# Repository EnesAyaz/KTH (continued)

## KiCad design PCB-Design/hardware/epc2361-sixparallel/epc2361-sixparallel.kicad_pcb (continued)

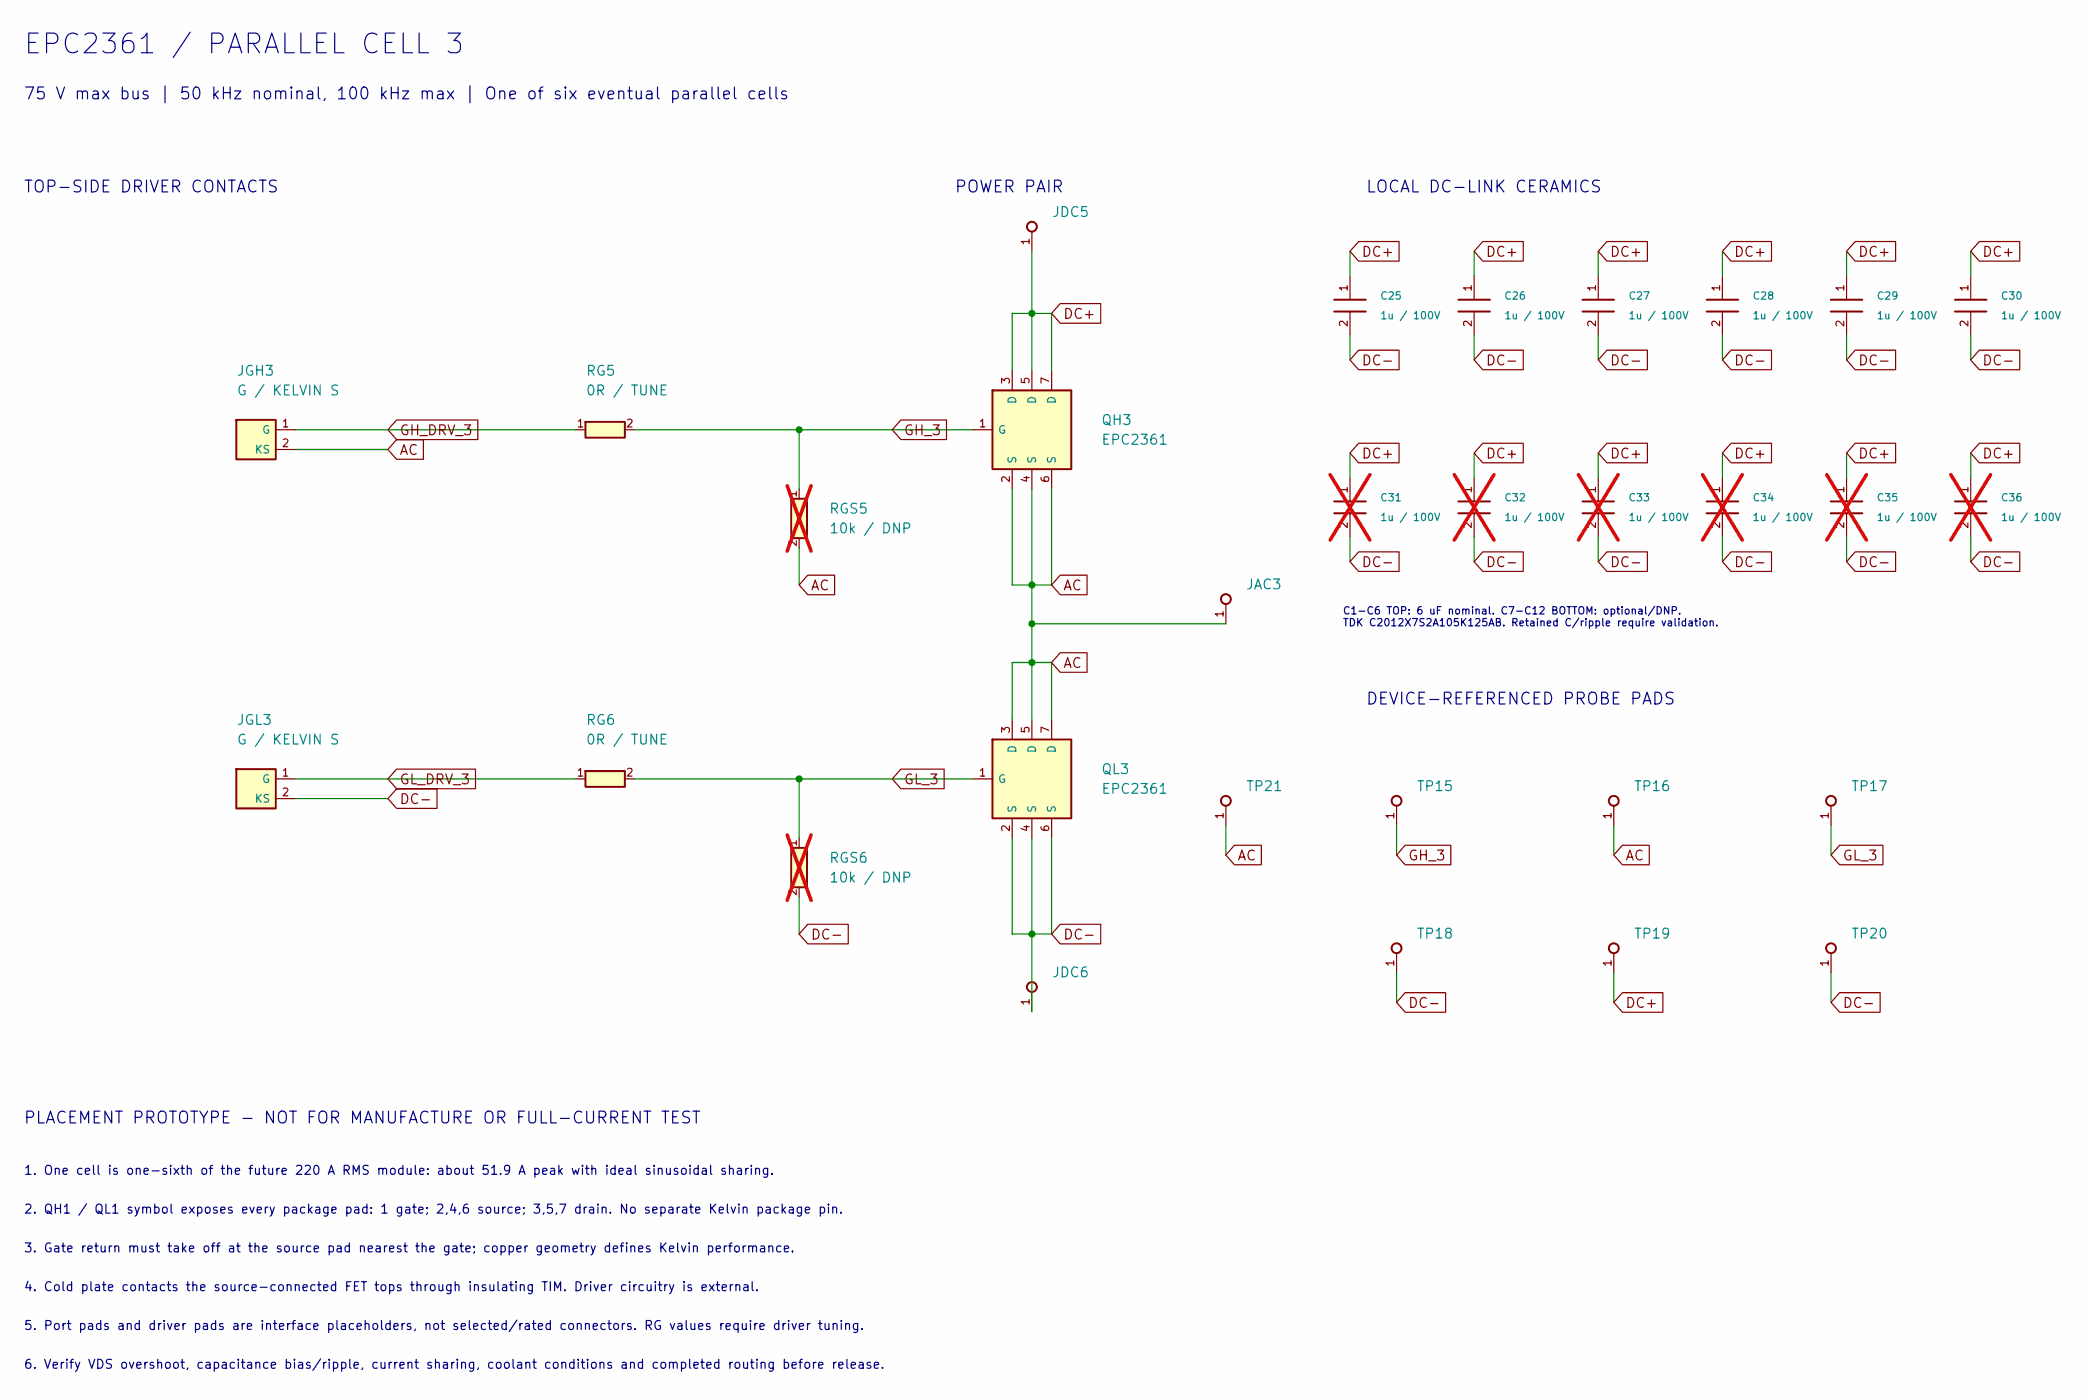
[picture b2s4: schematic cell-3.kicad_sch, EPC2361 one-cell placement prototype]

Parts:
C25, C26, C27, C28, C29, C30: 1u / 100V; C_0805_2012Metric
C31, C32, C33, C34, C35, C36: 1u / 100V; C_0805_2012Metric; not fitted
JAC3: AC PORT PAD; Power_Port_Pad
JDC5: DC+ PORT PAD; Power_Port_Pad
JDC6: DC- PORT PAD; Power_Port_Pad
JGH3: G / KELVIN S; Gate_Source_Pads
JGL3: G / KELVIN S; Gate_Source_Pads
QH3: EPC2361
QL3: EPC2361
RG5, RG6: 0R / TUNE; R_0402_1005Metric
RGS5, RGS6: 10k / DNP; R_0402_1005Metric; not fitted
TP15: GH; Probe_Pad
TP16, TP21: AC; Probe_Pad
TP17: GL; Probe_Pad
TP18, TP20: DC-; Probe_Pad
TP19: DC+; Probe_Pad

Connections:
AC: JAC3.1, JGH3.2 (KS), QH3.2 (S), QH3.4 (S), QH3.6 (S), QL3.3 (D), QL3.5 (D), QL3.7 (D), RGS5.2, TP16.1, TP21.1; also elsewhere on the board
DC+: C25.1, C26.1, C27.1, C28.1, C29.1, C30.1, C31.1, C32.1, C33.1, C34.1, C35.1, C36.1, JDC5.1, QH3.3 (D), QH3.5 (D), QH3.7 (D), TP19.1; also elsewhere on the board
DC-: C25.2, C26.2, C27.2, C28.2, C29.2, C30.2, C31.2, C32.2, C33.2, C34.2, C35.2, C36.2, JDC6.1, JGL3.2 (KS), QL3.2 (S), QL3.4 (S), QL3.6 (S), RGS6.2, TP18.1, TP20.1; also elsewhere on the board
GH_3: QH3.1 (G), RG5.2, RGS5.1, TP15.1
GH_DRV_3: JGH3.1 (G), RG5.1
GL_3: QL3.1 (G), RG6.2, RGS6.1, TP17.1
GL_DRV_3: JGL3.1 (G), RG6.1

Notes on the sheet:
EPC2361 / PARALLEL CELL 3
75 V max bus | 50 kHz nominal, 100 kHz max | One of six eventual parallel cells
TOP-SIDE DRIVER CONTACTS
POWER PAIR
LOCAL DC-LINK CERAMICS
C1-C6 TOP: 6 uF nominal. C7-C12 BOTTOM: optional/DNP. TDK C2012X7S2A105K125AB. Retained C/ripple require validation.
DEVICE-REFERENCED PROBE PADS
PLACEMENT PROTOTYPE - NOT FOR MANUFACTURE OR FULL-CURRENT TEST
1. One cell is one-sixth of the future 220 A RMS module: about 51.9 A peak with ideal sinusoidal sharing.
2. QH1 / QL1 symbol exposes every package pad: 1 gate; 2,4,6 source; 3,5,7 drain. No separate Kelvin package pin.
3. Gate return must take off at the source pad nearest the gate; copper geometry defines Kelvin performance.
4. Cold plate contacts the source-connected FET tops through insulating TIM. Driver circuitry is external.
5. Port pads and driver pads are interface placeholders, not selected/rated connectors. RG values require driver tuning.
6. Verify VDS overshoot, capacitance bias/ripple, current sharing, coolant conditions and completed routing before release.

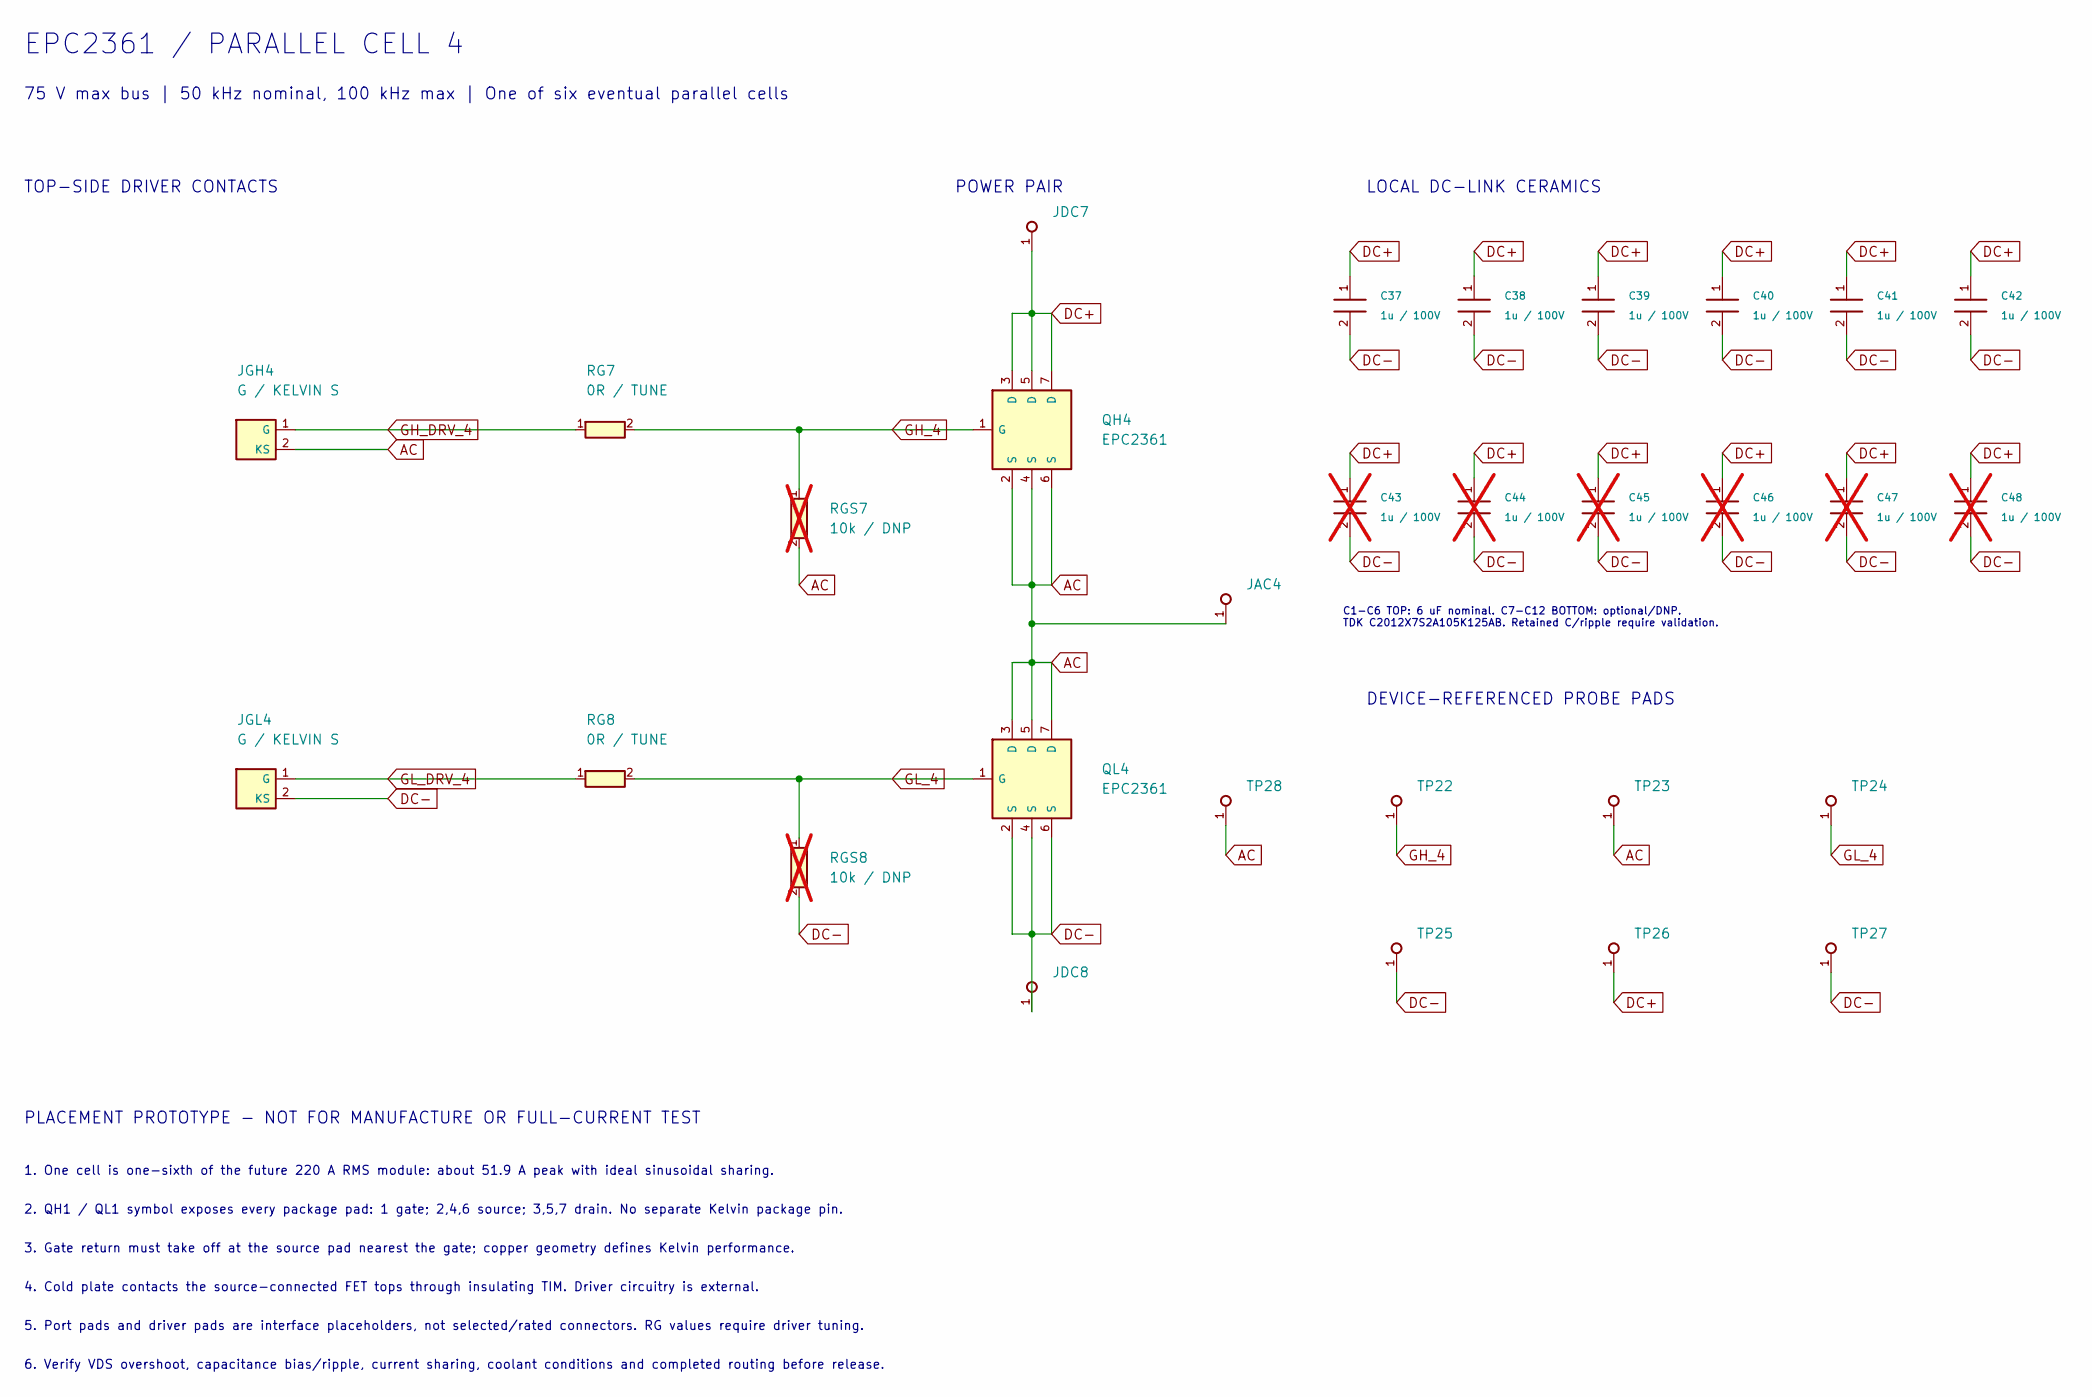
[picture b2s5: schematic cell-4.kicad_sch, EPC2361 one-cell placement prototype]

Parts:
C37, C38, C39, C40, C41, C42: 1u / 100V; C_0805_2012Metric
C43, C44, C45, C46, C47, C48: 1u / 100V; C_0805_2012Metric; not fitted
JAC4: AC PORT PAD; Power_Port_Pad
JDC7: DC+ PORT PAD; Power_Port_Pad
JDC8: DC- PORT PAD; Power_Port_Pad
JGH4: G / KELVIN S; Gate_Source_Pads
JGL4: G / KELVIN S; Gate_Source_Pads
QH4: EPC2361
QL4: EPC2361
RG7, RG8: 0R / TUNE; R_0402_1005Metric
RGS7, RGS8: 10k / DNP; R_0402_1005Metric; not fitted
TP22: GH; Probe_Pad
TP23, TP28: AC; Probe_Pad
TP24: GL; Probe_Pad
TP25, TP27: DC-; Probe_Pad
TP26: DC+; Probe_Pad

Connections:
AC: JAC4.1, JGH4.2 (KS), QH4.2 (S), QH4.4 (S), QH4.6 (S), QL4.3 (D), QL4.5 (D), QL4.7 (D), RGS7.2, TP23.1, TP28.1; also elsewhere on the board
DC+: C37.1, C38.1, C39.1, C40.1, C41.1, C42.1, C43.1, C44.1, C45.1, C46.1, C47.1, C48.1, JDC7.1, QH4.3 (D), QH4.5 (D), QH4.7 (D), TP26.1; also elsewhere on the board
DC-: C37.2, C38.2, C39.2, C40.2, C41.2, C42.2, C43.2, C44.2, C45.2, C46.2, C47.2, C48.2, JDC8.1, JGL4.2 (KS), QL4.2 (S), QL4.4 (S), QL4.6 (S), RGS8.2, TP25.1, TP27.1; also elsewhere on the board
GH_4: QH4.1 (G), RG7.2, RGS7.1, TP22.1
GH_DRV_4: JGH4.1 (G), RG7.1
GL_4: QL4.1 (G), RG8.2, RGS8.1, TP24.1
GL_DRV_4: JGL4.1 (G), RG8.1

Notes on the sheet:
EPC2361 / PARALLEL CELL 4
75 V max bus | 50 kHz nominal, 100 kHz max | One of six eventual parallel cells
TOP-SIDE DRIVER CONTACTS
POWER PAIR
LOCAL DC-LINK CERAMICS
C1-C6 TOP: 6 uF nominal. C7-C12 BOTTOM: optional/DNP. TDK C2012X7S2A105K125AB. Retained C/ripple require validation.
DEVICE-REFERENCED PROBE PADS
PLACEMENT PROTOTYPE - NOT FOR MANUFACTURE OR FULL-CURRENT TEST
1. One cell is one-sixth of the future 220 A RMS module: about 51.9 A peak with ideal sinusoidal sharing.
2. QH1 / QL1 symbol exposes every package pad: 1 gate; 2,4,6 source; 3,5,7 drain. No separate Kelvin package pin.
3. Gate return must take off at the source pad nearest the gate; copper geometry defines Kelvin performance.
4. Cold plate contacts the source-connected FET tops through insulating TIM. Driver circuitry is external.
5. Port pads and driver pads are interface placeholders, not selected/rated connectors. RG values require driver tuning.
6. Verify VDS overshoot, capacitance bias/ripple, current sharing, coolant conditions and completed routing before release.

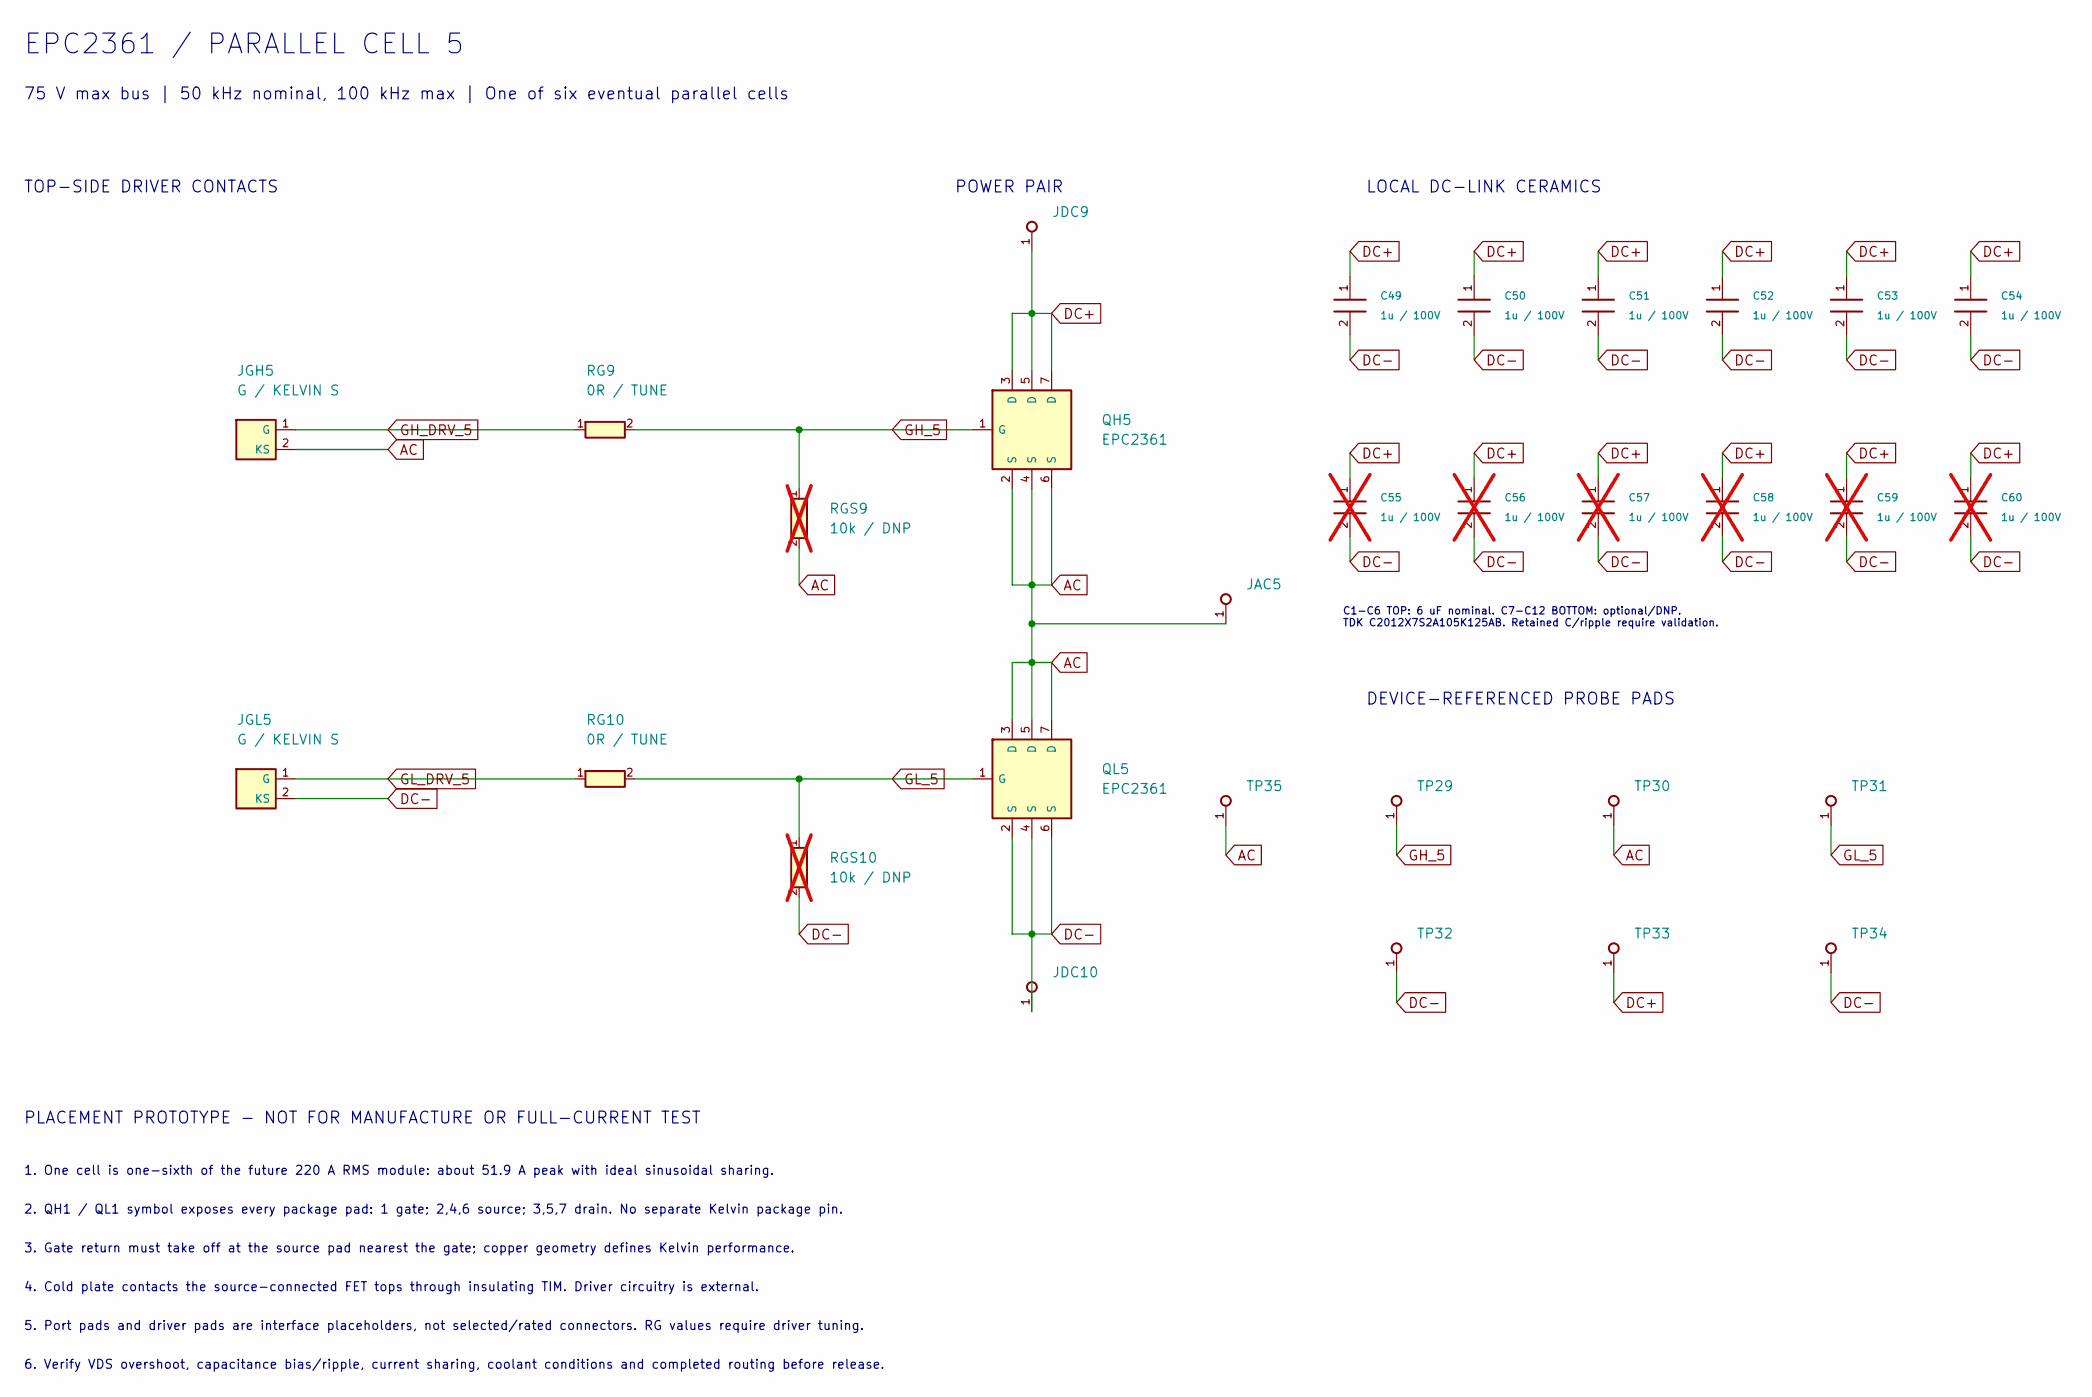
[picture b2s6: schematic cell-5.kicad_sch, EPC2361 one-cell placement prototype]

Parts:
C49, C50, C51, C52, C53, C54: 1u / 100V; C_0805_2012Metric
C55, C56, C57, C58, C59, C60: 1u / 100V; C_0805_2012Metric; not fitted
JAC5: AC PORT PAD; Power_Port_Pad
JDC9: DC+ PORT PAD; Power_Port_Pad
JDC10: DC- PORT PAD; Power_Port_Pad
JGH5: G / KELVIN S; Gate_Source_Pads
JGL5: G / KELVIN S; Gate_Source_Pads
QH5: EPC2361
QL5: EPC2361
RG9, RG10: 0R / TUNE; R_0402_1005Metric
RGS9, RGS10: 10k / DNP; R_0402_1005Metric; not fitted
TP29: GH; Probe_Pad
TP30, TP35: AC; Probe_Pad
TP31: GL; Probe_Pad
TP32, TP34: DC-; Probe_Pad
TP33: DC+; Probe_Pad

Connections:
AC: JAC5.1, JGH5.2 (KS), QH5.2 (S), QH5.4 (S), QH5.6 (S), QL5.3 (D), QL5.5 (D), QL5.7 (D), RGS9.2, TP30.1, TP35.1; also elsewhere on the board
DC+: C49.1, C50.1, C51.1, C52.1, C53.1, C54.1, C55.1, C56.1, C57.1, C58.1, C59.1, C60.1, JDC9.1, QH5.3 (D), QH5.5 (D), QH5.7 (D), TP33.1; also elsewhere on the board
DC-: C49.2, C50.2, C51.2, C52.2, C53.2, C54.2, C55.2, C56.2, C57.2, C58.2, C59.2, C60.2, JDC10.1, JGL5.2 (KS), QL5.2 (S), QL5.4 (S), QL5.6 (S), RGS10.2, TP32.1, TP34.1; also elsewhere on the board
GH_5: QH5.1 (G), RG9.2, RGS9.1, TP29.1
GH_DRV_5: JGH5.1 (G), RG9.1
GL_5: QL5.1 (G), RG10.2, RGS10.1, TP31.1
GL_DRV_5: JGL5.1 (G), RG10.1

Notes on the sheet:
EPC2361 / PARALLEL CELL 5
75 V max bus | 50 kHz nominal, 100 kHz max | One of six eventual parallel cells
TOP-SIDE DRIVER CONTACTS
POWER PAIR
LOCAL DC-LINK CERAMICS
C1-C6 TOP: 6 uF nominal. C7-C12 BOTTOM: optional/DNP. TDK C2012X7S2A105K125AB. Retained C/ripple require validation.
DEVICE-REFERENCED PROBE PADS
PLACEMENT PROTOTYPE - NOT FOR MANUFACTURE OR FULL-CURRENT TEST
1. One cell is one-sixth of the future 220 A RMS module: about 51.9 A peak with ideal sinusoidal sharing.
2. QH1 / QL1 symbol exposes every package pad: 1 gate; 2,4,6 source; 3,5,7 drain. No separate Kelvin package pin.
3. Gate return must take off at the source pad nearest the gate; copper geometry defines Kelvin performance.
4. Cold plate contacts the source-connected FET tops through insulating TIM. Driver circuitry is external.
5. Port pads and driver pads are interface placeholders, not selected/rated connectors. RG values require driver tuning.
6. Verify VDS overshoot, capacitance bias/ripple, current sharing, coolant conditions and completed routing before release.

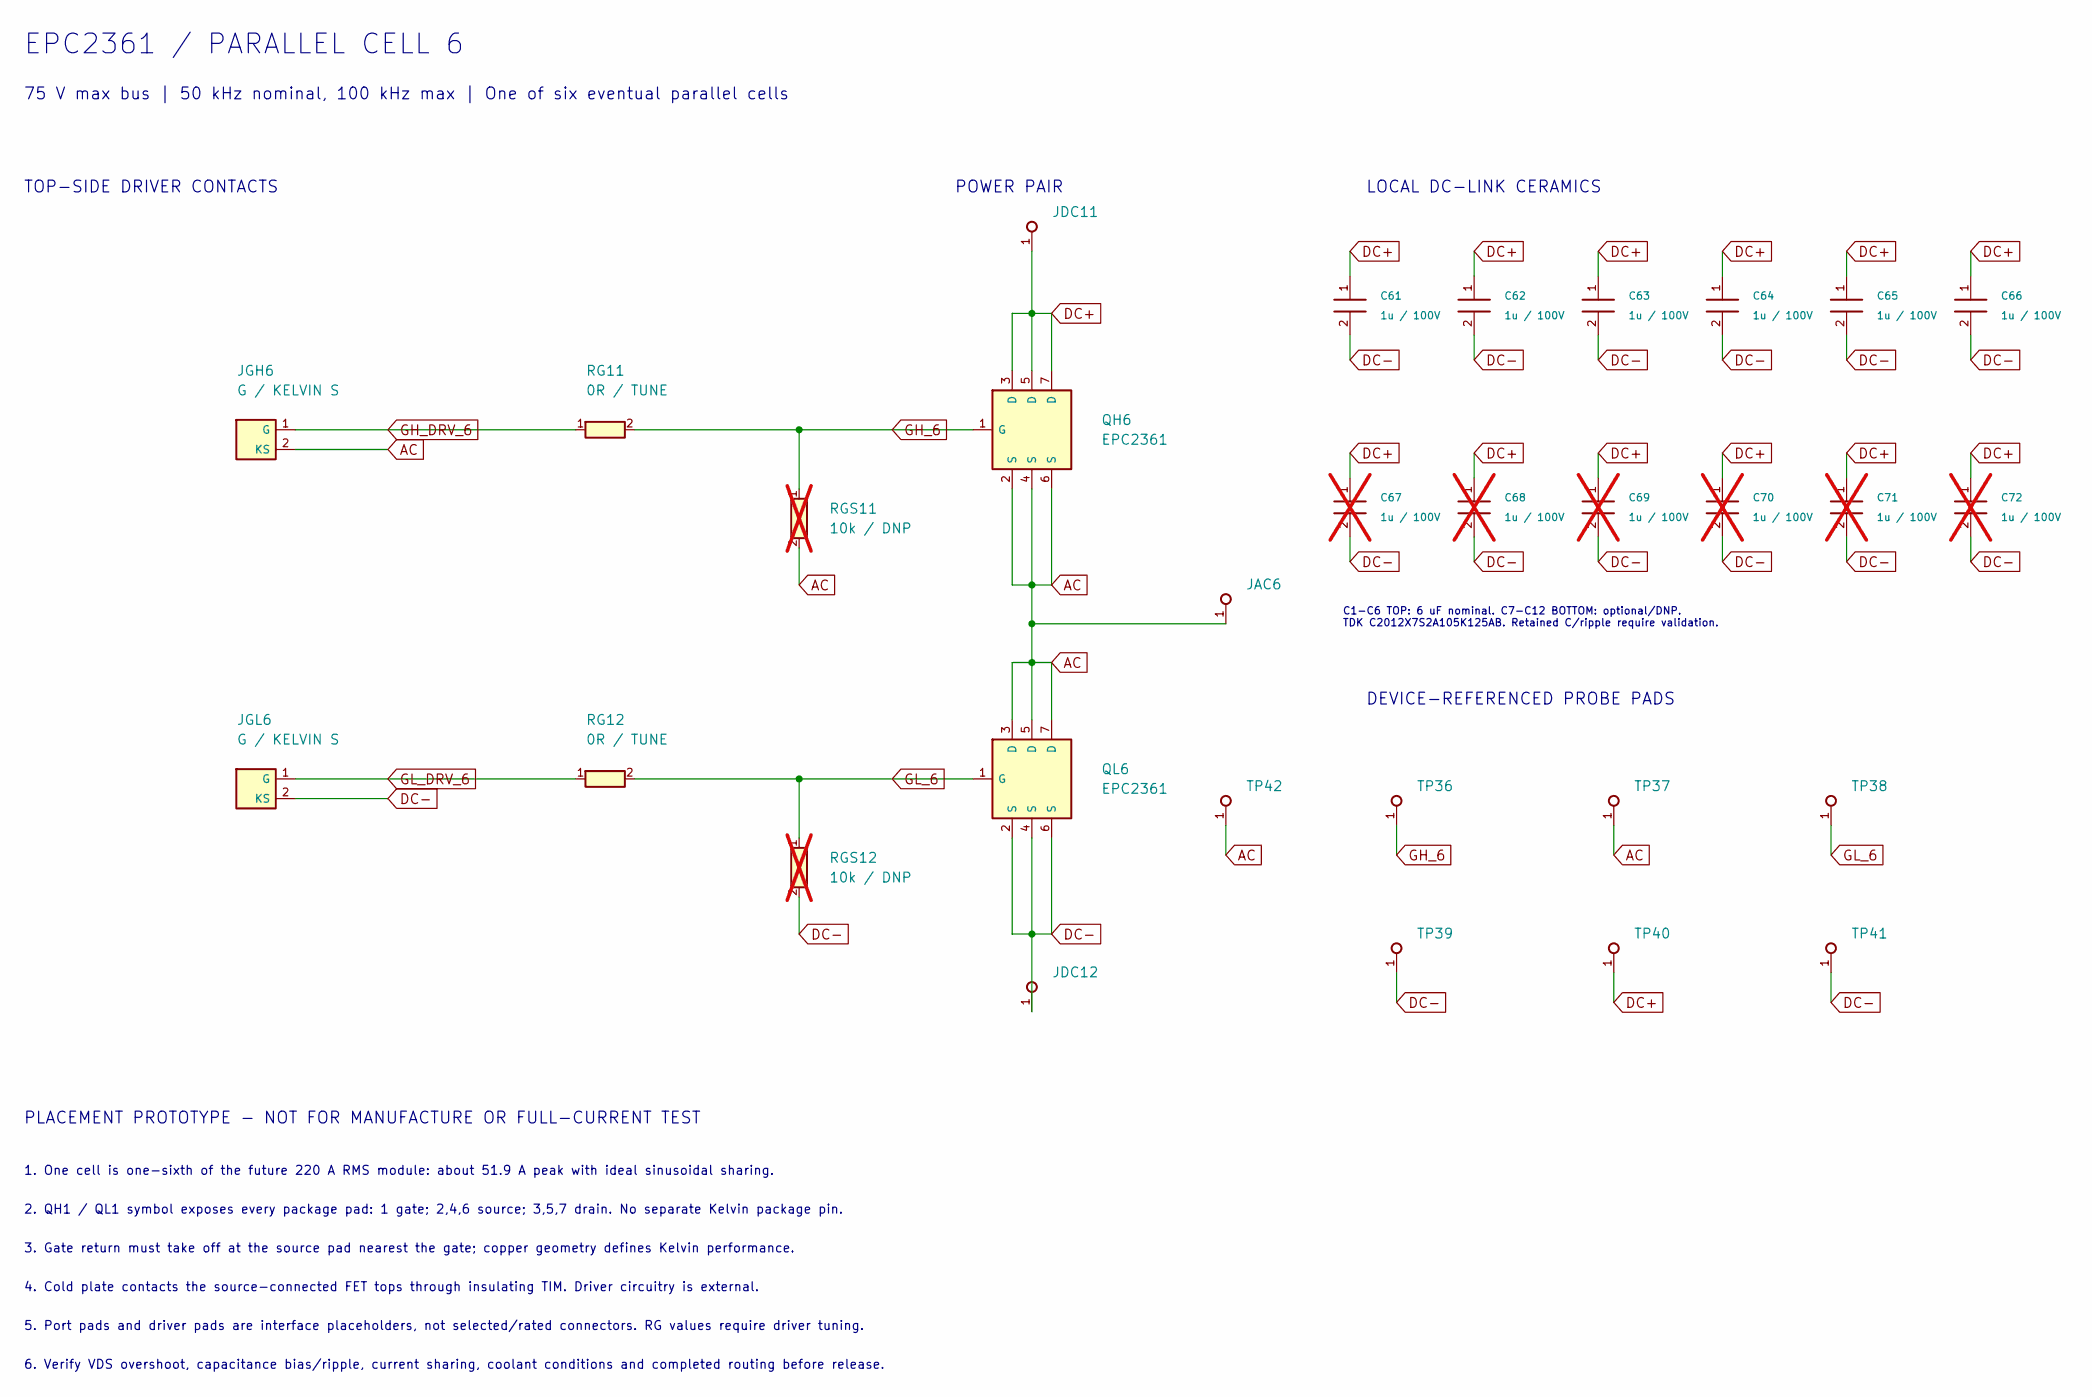
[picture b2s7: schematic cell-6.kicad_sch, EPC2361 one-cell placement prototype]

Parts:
C61, C62, C63, C64, C65, C66: 1u / 100V; C_0805_2012Metric
C67, C68, C69, C70, C71, C72: 1u / 100V; C_0805_2012Metric; not fitted
JAC6: AC PORT PAD; Power_Port_Pad
JDC11: DC+ PORT PAD; Power_Port_Pad
JDC12: DC- PORT PAD; Power_Port_Pad
JGH6: G / KELVIN S; Gate_Source_Pads
JGL6: G / KELVIN S; Gate_Source_Pads
QH6: EPC2361
QL6: EPC2361
RG11, RG12: 0R / TUNE; R_0402_1005Metric
RGS11, RGS12: 10k / DNP; R_0402_1005Metric; not fitted
TP36: GH; Probe_Pad
TP37, TP42: AC; Probe_Pad
TP38: GL; Probe_Pad
TP39, TP41: DC-; Probe_Pad
TP40: DC+; Probe_Pad

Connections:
AC: JAC6.1, JGH6.2 (KS), QH6.2 (S), QH6.4 (S), QH6.6 (S), QL6.3 (D), QL6.5 (D), QL6.7 (D), RGS11.2, TP37.1, TP42.1; also elsewhere on the board
DC+: C61.1, C62.1, C63.1, C64.1, C65.1, C66.1, C67.1, C68.1, C69.1, C70.1, C71.1, C72.1, JDC11.1, QH6.3 (D), QH6.5 (D), QH6.7 (D), TP40.1; also elsewhere on the board
DC-: C61.2, C62.2, C63.2, C64.2, C65.2, C66.2, C67.2, C68.2, C69.2, C70.2, C71.2, C72.2, JDC12.1, JGL6.2 (KS), QL6.2 (S), QL6.4 (S), QL6.6 (S), RGS12.2, TP39.1, TP41.1; also elsewhere on the board
GH_6: QH6.1 (G), RG11.2, RGS11.1, TP36.1
GH_DRV_6: JGH6.1 (G), RG11.1
GL_6: QL6.1 (G), RG12.2, RGS12.1, TP38.1
GL_DRV_6: JGL6.1 (G), RG12.1

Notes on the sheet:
EPC2361 / PARALLEL CELL 6
75 V max bus | 50 kHz nominal, 100 kHz max | One of six eventual parallel cells
TOP-SIDE DRIVER CONTACTS
POWER PAIR
LOCAL DC-LINK CERAMICS
C1-C6 TOP: 6 uF nominal. C7-C12 BOTTOM: optional/DNP. TDK C2012X7S2A105K125AB. Retained C/ripple require validation.
DEVICE-REFERENCED PROBE PADS
PLACEMENT PROTOTYPE - NOT FOR MANUFACTURE OR FULL-CURRENT TEST
1. One cell is one-sixth of the future 220 A RMS module: about 51.9 A peak with ideal sinusoidal sharing.
2. QH1 / QL1 symbol exposes every package pad: 1 gate; 2,4,6 source; 3,5,7 drain. No separate Kelvin package pin.
3. Gate return must take off at the source pad nearest the gate; copper geometry defines Kelvin performance.
4. Cold plate contacts the source-connected FET tops through insulating TIM. Driver circuitry is external.
5. Port pads and driver pads are interface placeholders, not selected/rated connectors. RG values require driver tuning.
6. Verify VDS overshoot, capacitance bias/ripple, current sharing, coolant conditions and completed routing before release.

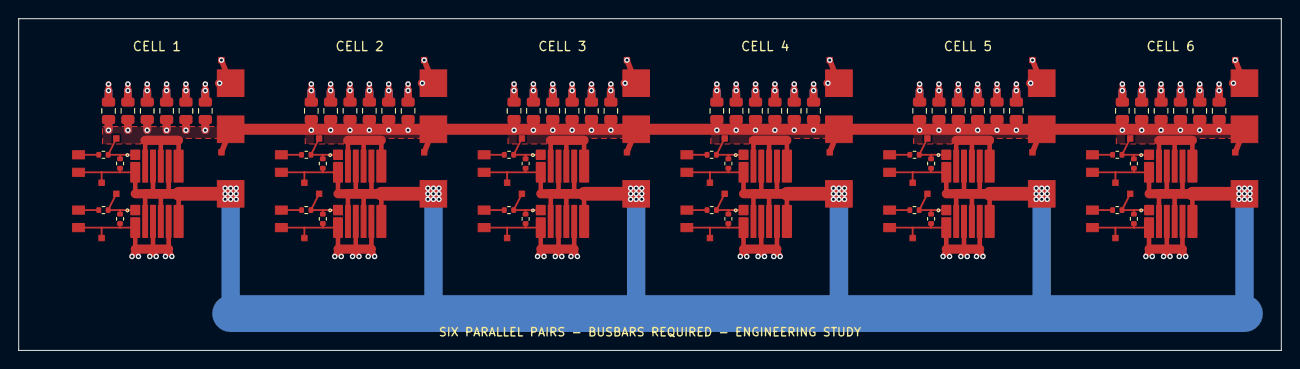
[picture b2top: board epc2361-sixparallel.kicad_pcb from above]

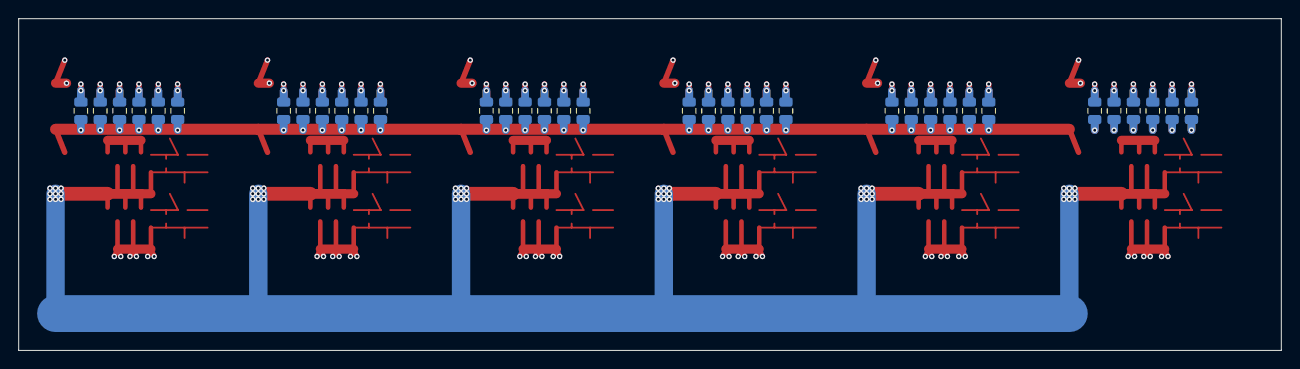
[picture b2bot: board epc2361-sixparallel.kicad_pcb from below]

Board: 4 copper layers, 137.0 x 36.0 mm, 180 parts (36 on the bottom side), 27 nets.

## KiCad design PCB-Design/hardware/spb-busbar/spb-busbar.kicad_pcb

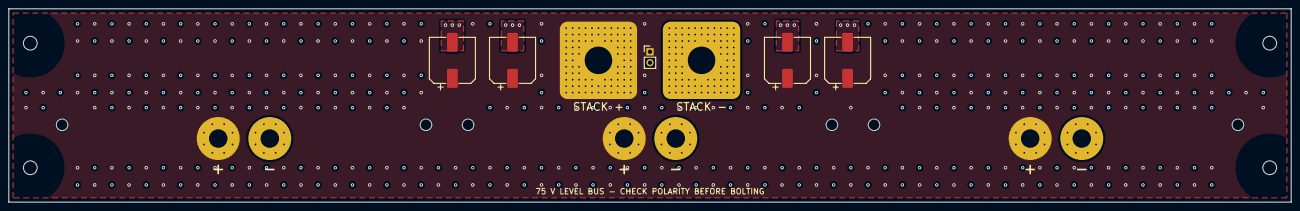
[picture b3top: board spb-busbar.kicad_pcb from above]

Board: 4 copper layers, 298.5 x 45.0 mm, 23 parts (0 on the bottom side), 2 nets, no tracks yet.

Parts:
C1, C2, C3, C4: DNP: 100 V hybrid polymer ~20-30 mOhm ESR (dampin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; CP_Elec_10x10.5
H1, H2, H3, H4, H5, H6: nylon M2.5 standoff 6.5 mm (leg H3/H4); MountingHole_2.7mm_M2.5
H7, H8, H9, H10: M3 insulating standoff to frame (8 mm Cu keep-out); MountingHole_3.2mm_M3
J1: LEG1 DC+; BUS_M4_REDCUBE
J2: LEG1 DC-; BUS_M4_REDCUBE
J3: LEG2 DC+; BUS_M4_REDCUBE
J4: LEG2 DC-; BUS_M4_REDCUBE
J5: LEG3 DC+; BUS_M4_REDCUBE
J6: LEG3 DC-; BUS_M4_REDCUBE
J7: STACK DC+ (to level above: its DC-); BUS_LUG_M6
J8: STACK DC- (to level below: its DC+); BUS_LUG_M6
J9: LEVEL V: 1 DC+, 2 DC- (HV referenced); PinHeader_1x02_P2.54mm_Vertical

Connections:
DCN: C1.2, C2.2, C3.2, C4.2, J2.1, J4.1, J6.1, J8.1, J9.2
DCP: C1.1, C2.1, C3.1, C4.1, J1.1, J3.1, J5.1, J7.1, J9.1

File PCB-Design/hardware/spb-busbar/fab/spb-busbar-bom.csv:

"# 4 layers, 1.6 mm FR4, 2 oz on all layers (JLC3313 stack-up), ENIG, bolt pads without mask"
Qty,References,Value,Footprint,Manufacturer part / note,Fit
1,J9,"LEVEL V: 1 DC+, 2 DC- (HV referenced)",PinHeader_1x02_P2.54mm_Vertical,2.54 mm header 1x2,fit
4,C1 C2 C3 C4,"DNP: 100 V hybrid polymer ~20-30 mOhm ESR (damping, fit if ringing)",CP_Elec_10x10.5,"select: 100 V hybrid polymer, 10 x 10.5 mm SMD",DNP

Mechanical (not placed by the assembler)
6,J1-J6,M4 x 8 screw + washer into the leg REDCUBE terminals,-,"steel, A2"
6,H1-H6,nylon standoff M2.5 x 6.5 mm (leg H3/H4),-,nylon
4,H7-H10,"M3 insulating standoff to the frame (8 mm Cu keep-out, 1200 V)",-,PA66 / ceramic
2,J7-J8,"M6 ring lug + Cu braid to the level above / below, M6 bolt + nut",-,"Cu, tin plated"
